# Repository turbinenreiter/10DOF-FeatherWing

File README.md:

# 10DOF-FeatherWing

This is a daughter-board for Adafruits Feather boards.  

It features:
  * 3-axis accelerometer
  * 3-axis gyroscope
  * 3-axis magnetometer
  * temperature sensor
  * pressure sensor
  * humidity sensor
  * 8 servo headers (PWR from BAT)
  * SPI header
  * UART header
  * one green and one red LED
  * one switch
  * GPIO#9 (A7) is connected to BAT to measure it's voltage

The board has been produced and tested.
  * all sensors work
  * red LED works
  * green LED is on when connected to USB, but not battery - no idea why

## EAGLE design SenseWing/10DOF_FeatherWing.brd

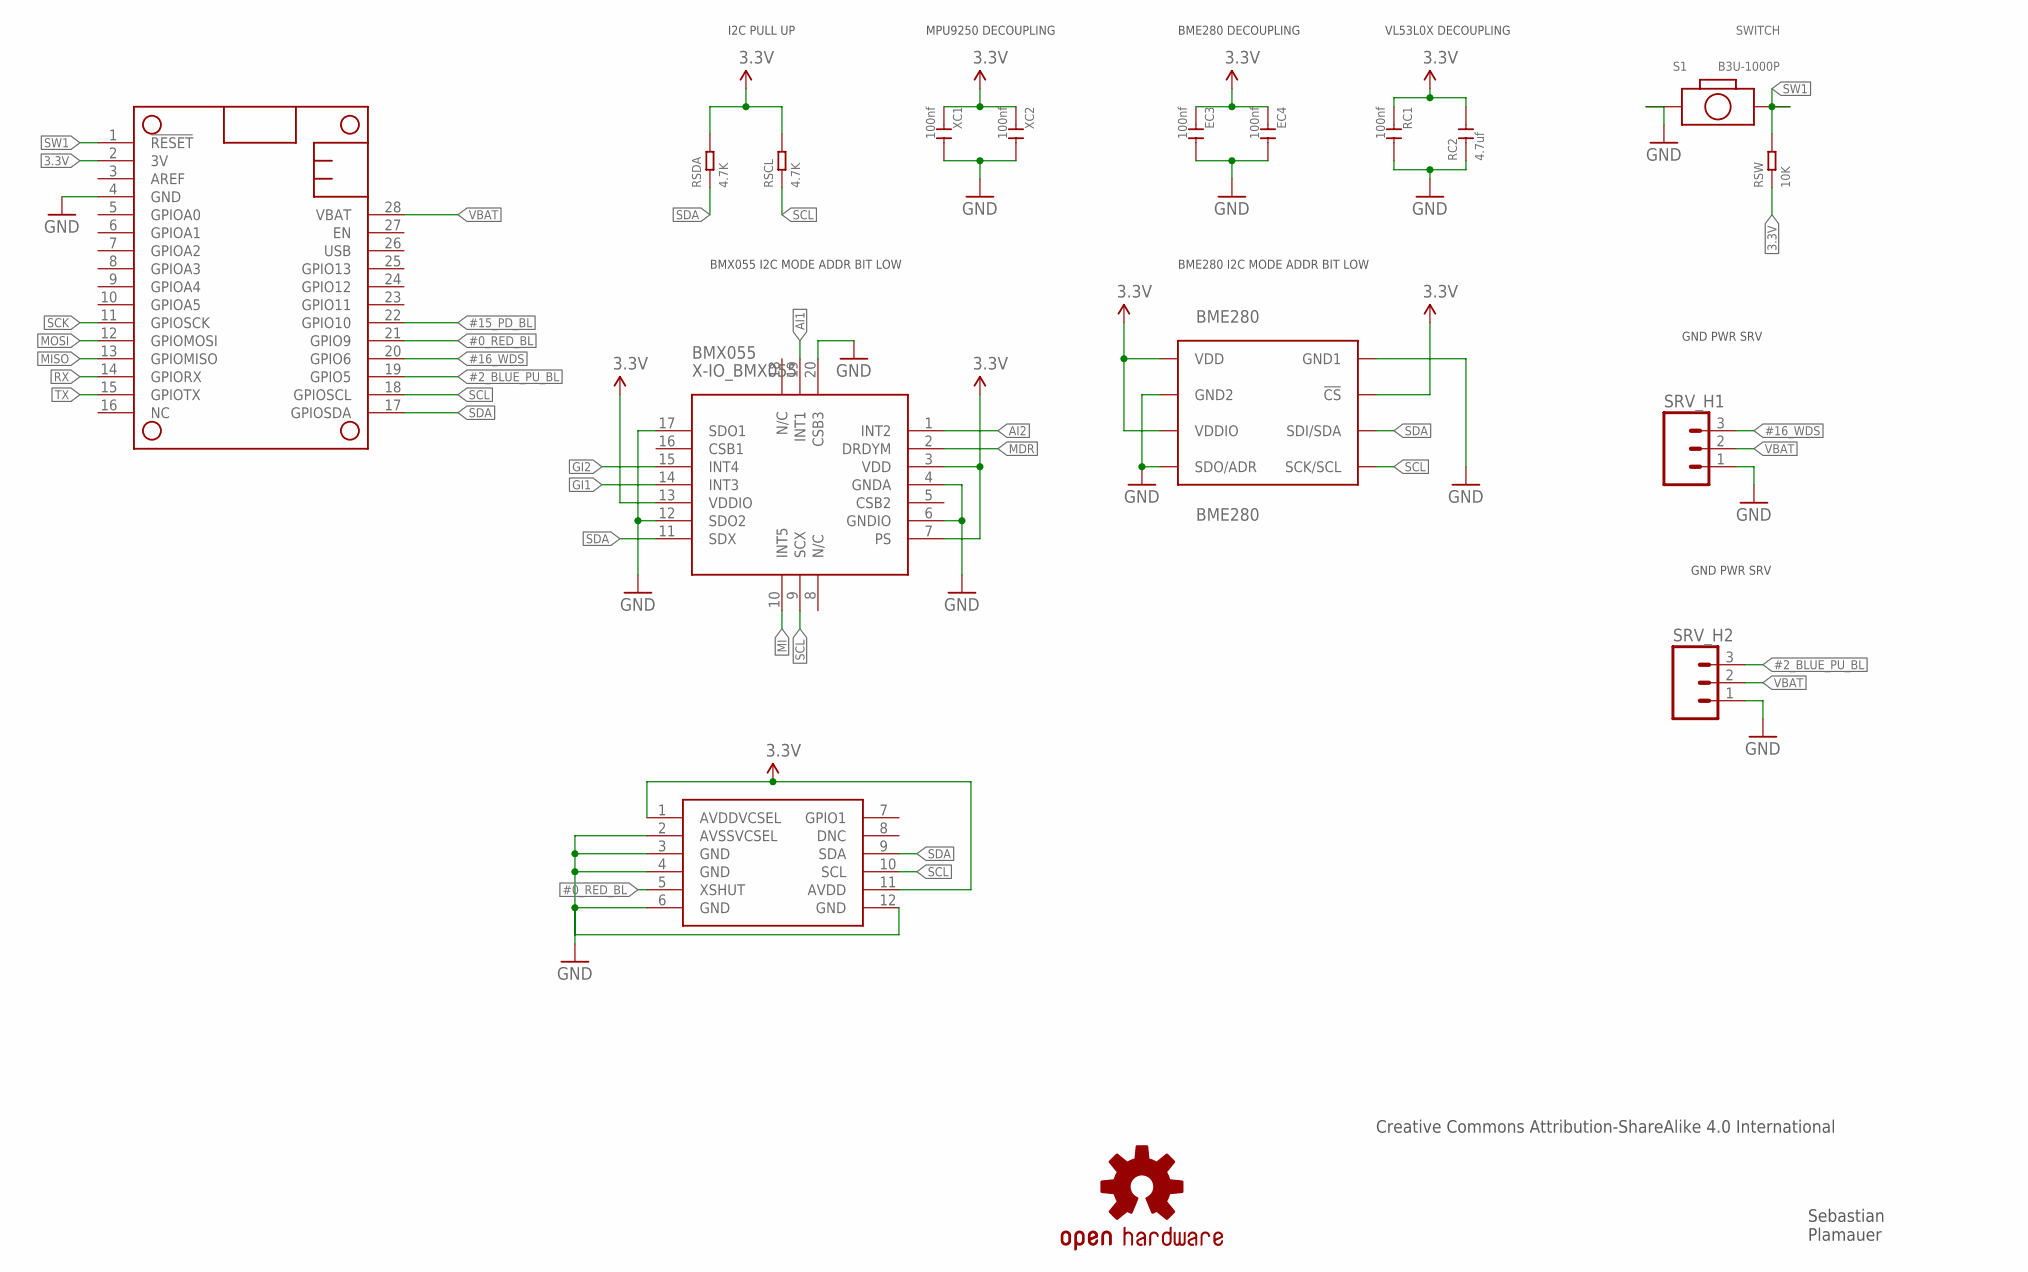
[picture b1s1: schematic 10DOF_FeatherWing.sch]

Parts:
BME280: BME280; BME280COMPONENTLIBRARY_BME280_LGA
BMX055: X-IO_BMX055
EC3, EC4: 100nf; C0603
LOGO1: OSHW-LOGOS; OSHW-LOGO-S
MS1: FEATHERWING
RC1: 100nf; C0603
RC2: 4.7uf; C0603
RSCL: 4.7K; R0603
RSDA: 4.7K; R0603
RSW: 10K; R0603
S1: B3U-1000P; SW2-SMD-3.0X2.5X1.2+0.4MM
SRV_H1, SRV_H2: M03PTH; 1X03
U$1: VL53L0X
XC1, XC2: 100nf; C0603

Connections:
3.3V: BME280.P$2 (!CS), BME280.P$6 (VDDIO), BME280.P$8 (VDD), BMX055.3 (VDD), BMX055.7 (PS), BMX055.13 (VDDIO), EC3.1, EC4.1, MS1.2 (3V), RC1.1, RC2.2, RSCL.2, RSDA.2, RSW.1, U$1.1 (AVDDVCSEL), U$1.11 (AVDD), XC1.1, XC2.1
#0_RED_BL: MS1.21 (GPIO9), U$1.5 (XSHUT)
#2_BLUE_PU_BL: MS1.19 (GPIO5), SRV_H2.3
#15_PD_BL: MS1.22 (GPIO10)
#16_WDS: MS1.20 (GPIO6), SRV_H1.3
AI1: BMX055.19 (INT1)
AI2: BMX055.1 (INT2)
GI1: BMX055.14 (INT3)
GI2: BMX055.15 (INT4)
GND: BME280.P$1 (GND1), BME280.P$5 (SDO/ADR), BME280.P$7 (GND2), BMX055.4 (GNDA), BMX055.6 (GNDIO), BMX055.12 (SDO2), BMX055.17 (SDO1), BMX055.20 (CSB3), EC3.2, EC4.2, MS1.4 (GND), RC1.2, RC2.1, S1.1, SRV_H1.1, SRV_H2.1, U$1.2 (AVSSVCSEL), U$1.3 (GND), U$1.4 (GND), U$1.6 (GND), U$1.12 (GND), XC1.2, XC2.2
MDR: BMX055.2 (DRDYM)
MI: BMX055.10 (INT5)
MISO: MS1.13 (GPIOMISO)
MOSI: MS1.12 (GPIOMOSI)
RX: MS1.14 (GPIORX)
SCK: MS1.11 (GPIOSCK)
SCL: BME280.P$4 (SCK/SCL), BMX055.9 (SCX), MS1.18 (GPIOSCL), RSCL.1, U$1.10 (SCL)
SDA: BME280.P$3 (SDI/SDA), BMX055.11 (SDX), MS1.17 (GPIOSDA), RSDA.1, U$1.9 (SDA)
SW1: MS1.1 (!RESET), RSW.2, S1.2
TX: MS1.15 (GPIOTX)
VBAT: MS1.28 (VBAT), SRV_H1.2, SRV_H2.2

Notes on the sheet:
I2C PULL UP
MPU9250 DECOUPLING
BME280 DECOUPLING
BME280 I2C MODE ADDR BIT LOW
GND PWR SRV
SWITCH
Sebastian Plamauer
Creative Commons Attribution-ShareAlike 4.0 International
VL53L0X DECOUPLING
BMX055 I2C MODE ADDR BIT LOW

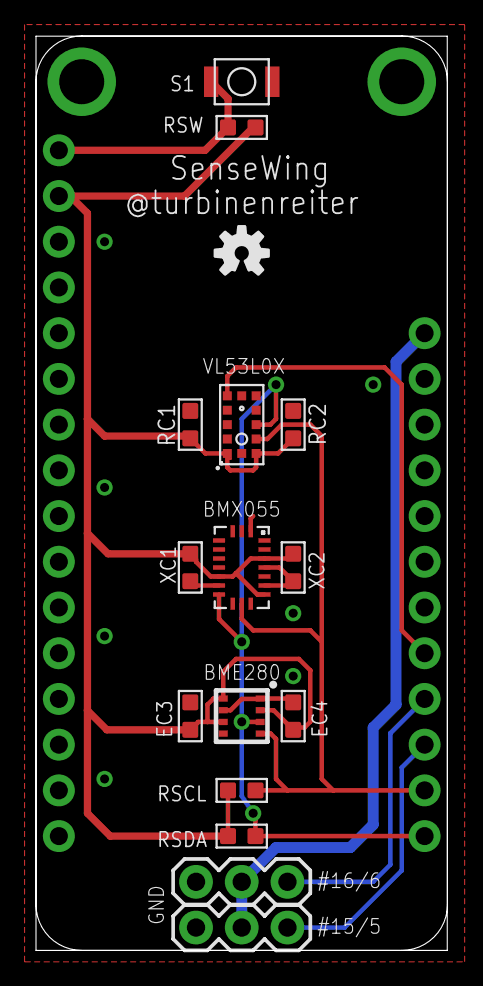
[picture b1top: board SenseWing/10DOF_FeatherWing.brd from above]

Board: 2 copper layers, 22.9 x 50.8 mm, 17 parts (0 on the bottom side), 9 nets.

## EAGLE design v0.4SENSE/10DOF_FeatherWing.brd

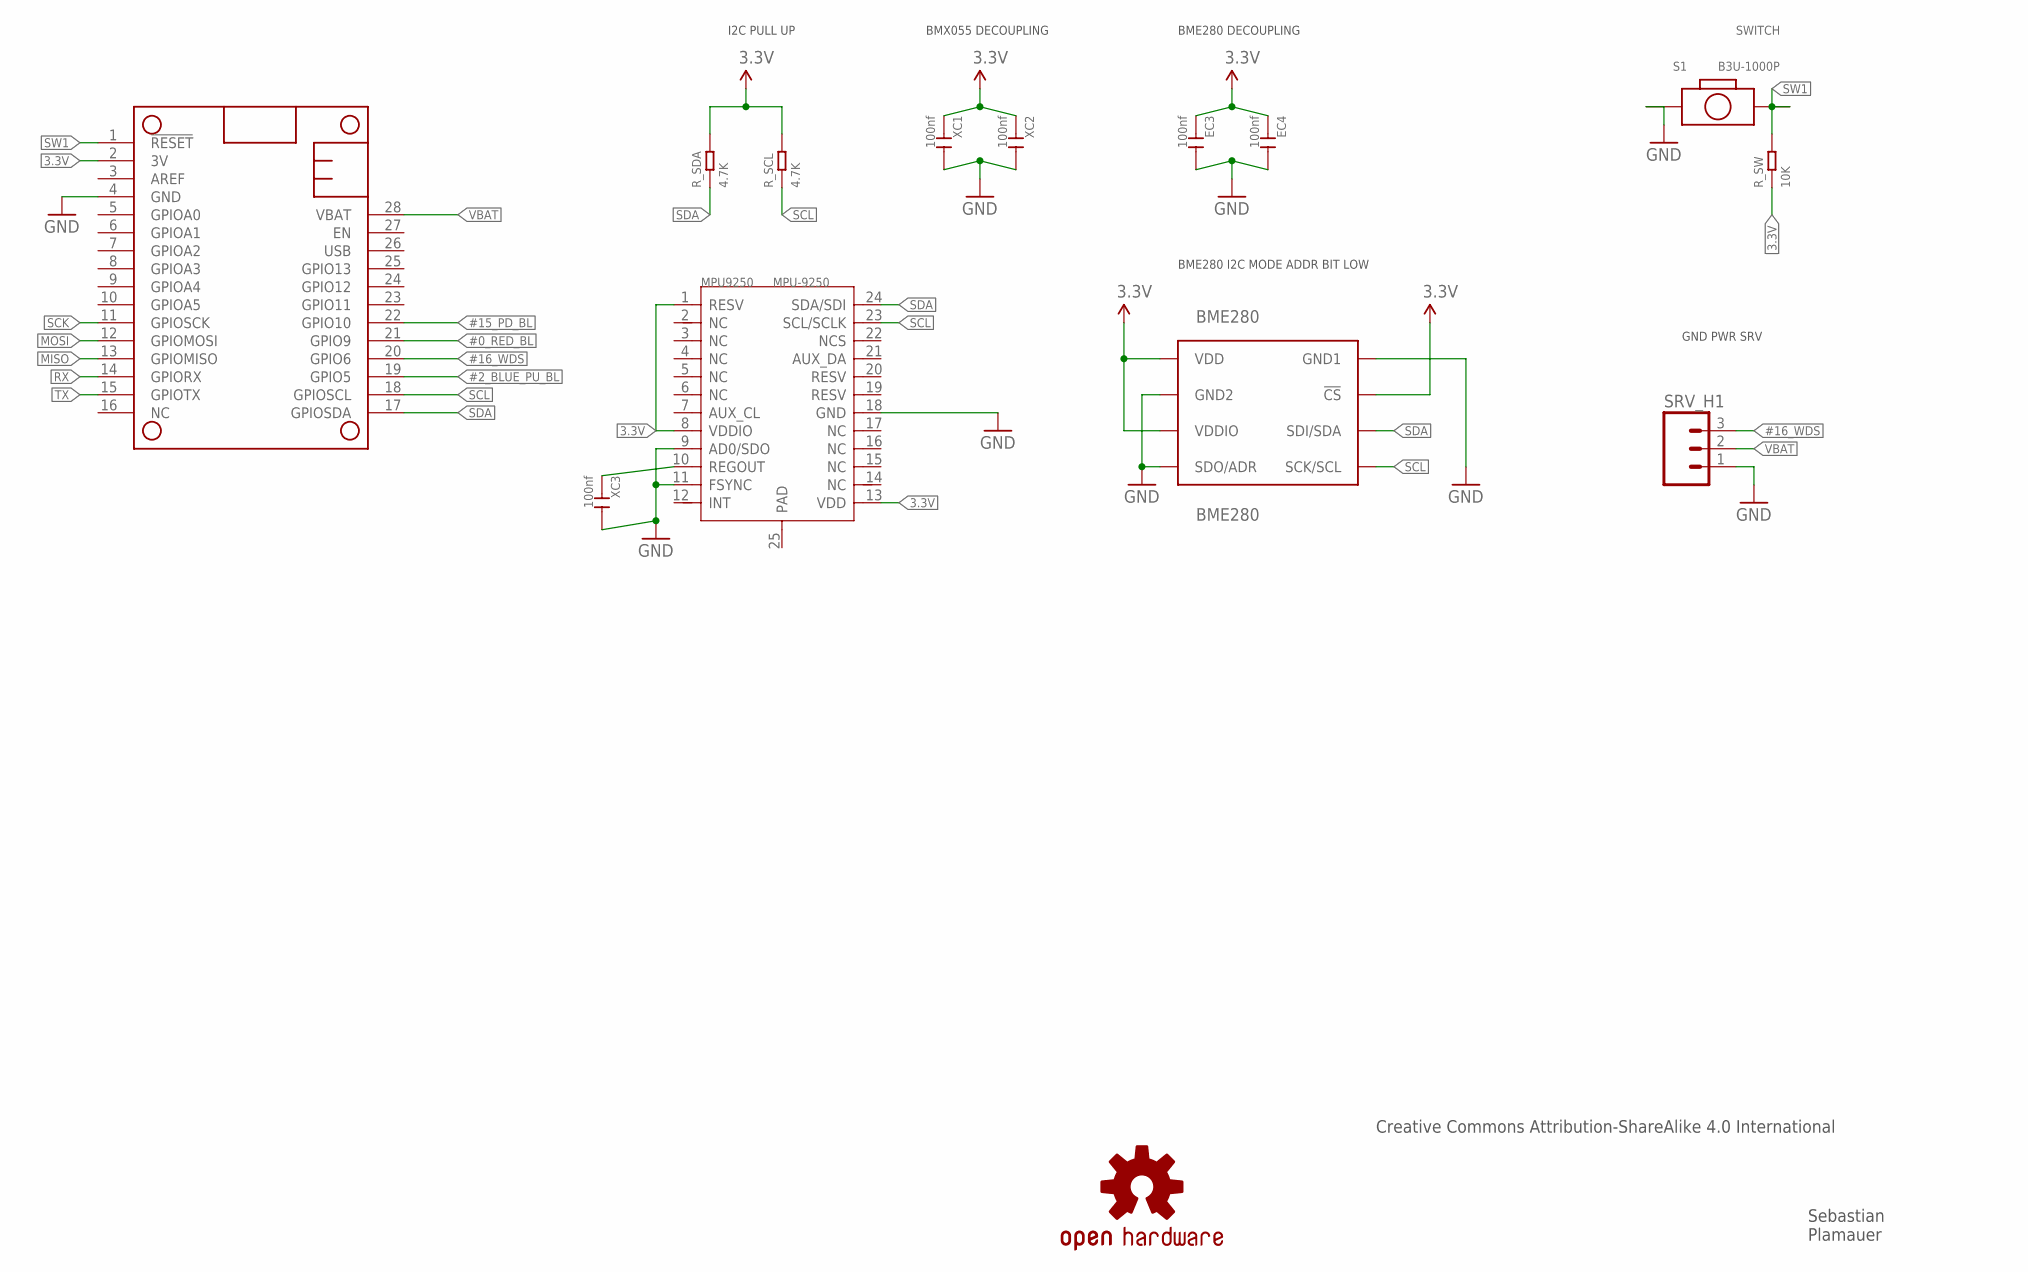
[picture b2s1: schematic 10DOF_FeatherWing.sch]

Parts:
BME280: BME280; BME280COMPONENTLIBRARY_BME280_LGA
EC3, EC4: 100nf; C0603
LOGO1: OSHW-LOGOS; OSHW-LOGO-S
MPU9250: MPU-9250; QFN24G-0.4-3X3MM
MS1: FEATHERWING
R_SCL: 4.7K; R0603
R_SDA: 4.7K; R0603
R_SW: 10K; R0603
S1: B3U-1000P; SW2-SMD-3.0X2.5X1.2+0.4MM
SRV_H1: M03PTH; 1X03
XC1, XC2, XC3: 100nf; C0603

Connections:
3.3V: BME280.P$2 (!CS), BME280.P$6 (VDDIO), BME280.P$8 (VDD), EC3.1, EC4.1, MPU9250.1 (RESV), MPU9250.8 (VDDIO), MPU9250.13 (VDD), MS1.2 (3V), R_SCL.2, R_SDA.2, R_SW.1, XC1.1, XC2.1
#0_RED_BL: MS1.21 (GPIO9)
#2_BLUE_PU_BL: MS1.19 (GPIO5)
#15_PD_BL: MS1.22 (GPIO10)
#16_WDS: MS1.20 (GPIO6), SRV_H1.3
GND: BME280.P$1 (GND1), BME280.P$5 (SDO/ADR), BME280.P$7 (GND2), EC3.2, EC4.2, MPU9250.9 (AD0/SDO), MPU9250.11 (FSYNC), MPU9250.18 (GND), MS1.4 (GND), S1.1, SRV_H1.1, XC1.2, XC2.2, XC3.2
MISO: MS1.13 (GPIOMISO)
MOSI: MS1.12 (GPIOMOSI)
unnamed: MPU9250.10 (REGOUT), XC3.1
RX: MS1.14 (GPIORX)
SCK: MS1.11 (GPIOSCK)
SCL: BME280.P$4 (SCK/SCL), MPU9250.23 (SCL/SCLK), MS1.18 (GPIOSCL), R_SCL.1
SDA: BME280.P$3 (SDI/SDA), MPU9250.24 (SDA/SDI), MS1.17 (GPIOSDA), R_SDA.1
SW1: MS1.1 (!RESET), R_SW.2, S1.2
TX: MS1.15 (GPIOTX)
VBAT: MS1.28 (VBAT), SRV_H1.2

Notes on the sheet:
I2C PULL UP
BMX055 DECOUPLING
BME280 DECOUPLING
BME280 I2C MODE ADDR BIT LOW
GND PWR SRV
SWITCH
Sebastian Plamauer
Creative Commons Attribution-ShareAlike 4.0 International

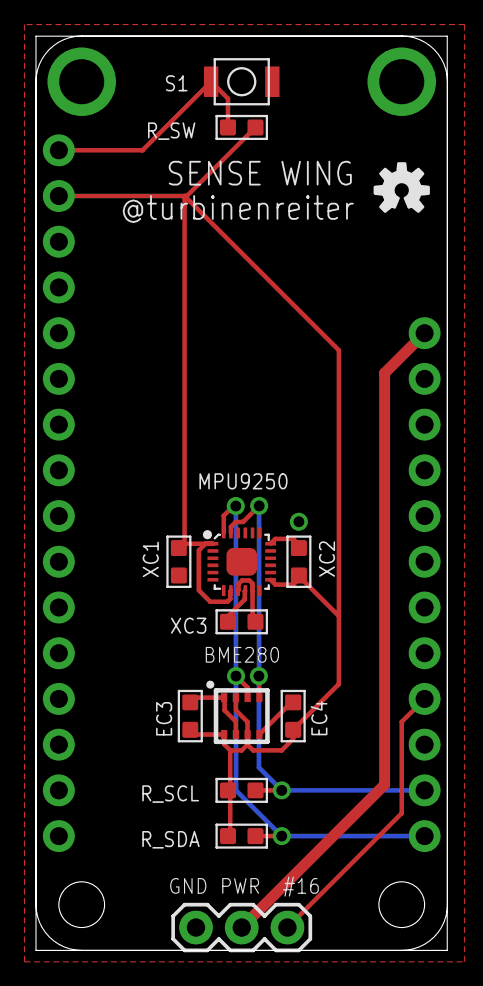
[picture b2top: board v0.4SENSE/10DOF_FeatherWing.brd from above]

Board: 2 copper layers, 22.9 x 50.8 mm, 14 parts (0 on the bottom side), 8 nets.

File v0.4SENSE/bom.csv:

"BME280","BME280","BME280COMPONENTLIBRARY_BME280","BME280COMPONENTLIBRARY_BME280_LGA"," ","1"
"EC3, EC4, XC1, XC2, XC3","100nf","CERAMIC-100NF-50V-10%-X7R(0603)","C0603","302010138","5"
"MPU9250","MPU-9250","MOTION/POSITION-MPU-9250(QFN24)","QFN24G-0.4-3X3MM","314990005","1"
"R_SCL, R_SDA","4.7K","SMD-RES-4.7K-5%-1/10W(0603)","R0603","301010290","2"
"R_SW","10K","SMD-RES-10K-1%-1/10W(0603)","R0603","301010299","1"
"S1","B3U-1000P","SMD-BUTTON-WITHOUT-BOSS-(2P-3X2.5MM)","SW2-SMD-3.0X2.5X1.2+0.4MM","311020047","1"

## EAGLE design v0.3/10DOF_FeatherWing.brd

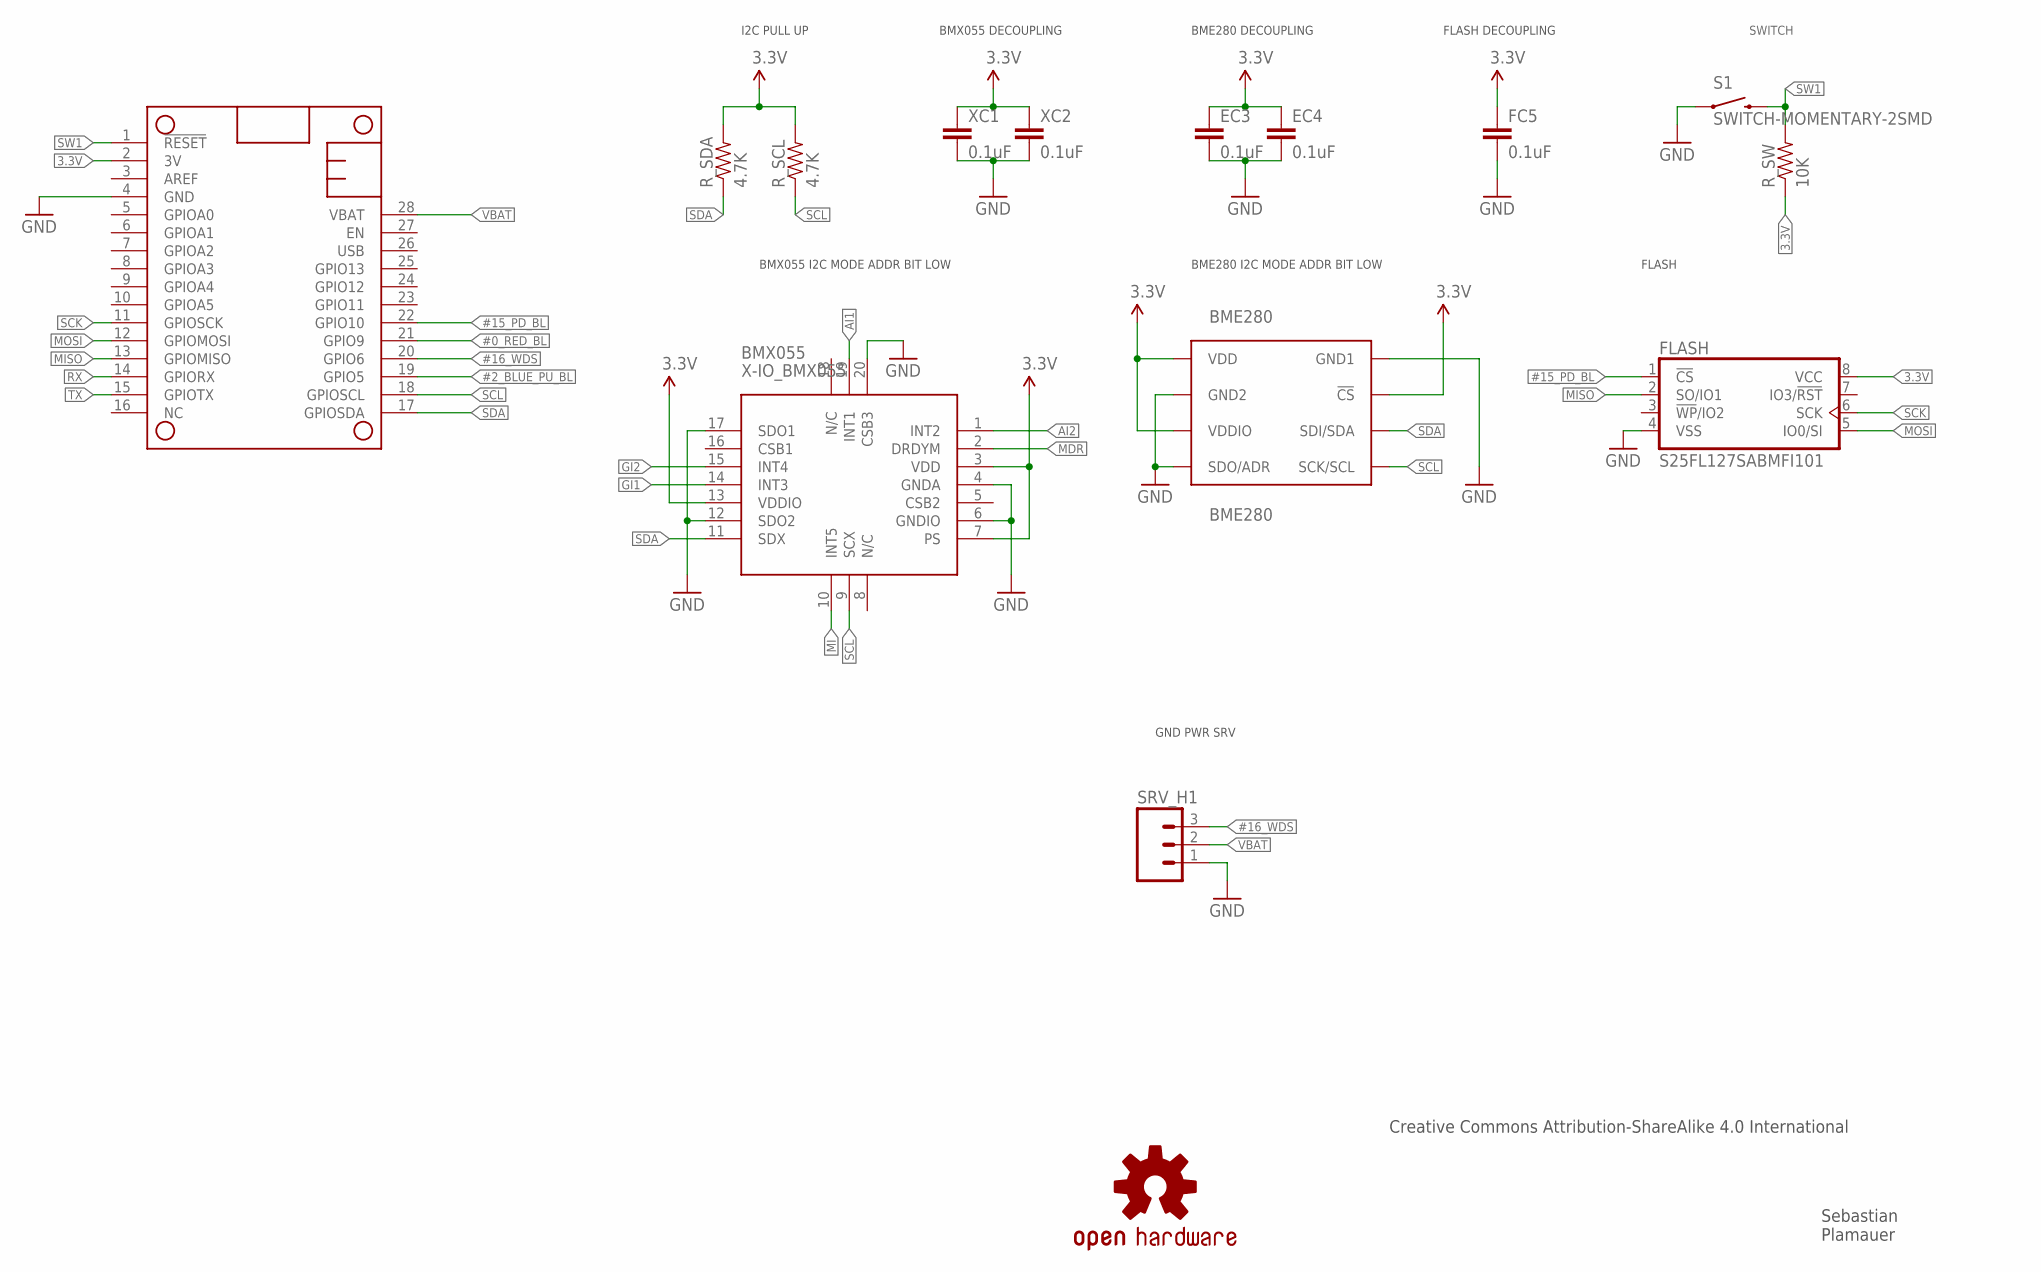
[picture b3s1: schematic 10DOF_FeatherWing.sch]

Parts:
BME280: BME280; BME280COMPONENTLIBRARY_BME280_LGA
BMX055: X-IO_BMX055
EC3, EC4: 0.1uF; 0603-CAP
FC5: 0.1uF; 0603-CAP
FLASH: S25FL127SABMFI101; SO08-S2A
LOGO1: OSHW-LOGOS; OSHW-LOGO-S
MS1: FEATHERWING
R_SCL: 4.7K; 0603-RES
R_SDA: 4.7K; 0603-RES
R_SW: 10K; 0603-RES
S1: SWITCH-MOMENTARY-2SMD; TACTILE-SWITCH-SMD
SRV_H1: M03PTH; 1X03
XC1, XC2: 0.1uF; 0603-CAP

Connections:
3.3V: BME280.P$2 (!CS), BME280.P$6 (VDDIO), BME280.P$8 (VDD), BMX055.3 (VDD), BMX055.7 (PS), BMX055.13 (VDDIO), EC3.1, EC4.1, FC5.1, FLASH.8 (VCC), MS1.2 (3V), R_SCL.2, R_SDA.2, R_SW.1, XC1.1, XC2.1
#0_RED_BL: MS1.21 (GPIO9)
#2_BLUE_PU_BL: MS1.19 (GPIO5)
#15_PD_BL: FLASH.1 (!CS!), MS1.22 (GPIO10)
#16_WDS: MS1.20 (GPIO6), SRV_H1.3
AI1: BMX055.19 (INT1)
AI2: BMX055.1 (INT2)
GI1: BMX055.14 (INT3)
GI2: BMX055.15 (INT4)
GND: BME280.P$1 (GND1), BME280.P$5 (SDO/ADR), BME280.P$7 (GND2), BMX055.4 (GNDA), BMX055.6 (GNDIO), BMX055.12 (SDO2), BMX055.17 (SDO1), BMX055.20 (CSB3), EC3.2, EC4.2, FC5.2, FLASH.4 (VSS), MS1.4 (GND), S1.1, SRV_H1.1, XC1.2, XC2.2
MDR: BMX055.2 (DRDYM)
MI: BMX055.10 (INT5)
MISO: FLASH.2 (SO/IO1), MS1.13 (GPIOMISO)
MOSI: FLASH.5 (IO0/SI), MS1.12 (GPIOMOSI)
RX: MS1.14 (GPIORX)
SCK: FLASH.6 (SCK), MS1.11 (GPIOSCK)
SCL: BME280.P$4 (SCK/SCL), BMX055.9 (SCX), MS1.18 (GPIOSCL), R_SCL.1
SDA: BME280.P$3 (SDI/SDA), BMX055.11 (SDX), MS1.17 (GPIOSDA), R_SDA.1
SW1: MS1.1 (!RESET), R_SW.2, S1.3 (2)
TX: MS1.15 (GPIOTX)
VBAT: MS1.28 (VBAT), SRV_H1.2

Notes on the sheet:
I2C PULL UP
BMX055 DECOUPLING
BME280 DECOUPLING
BME280 I2C MODE ADDR BIT LOW
BMX055 I2C MODE ADDR BIT LOW
GND PWR SRV
SWITCH
Sebastian Plamauer
Creative Commons Attribution-ShareAlike 4.0 International
FLASH
FLASH DECOUPLING

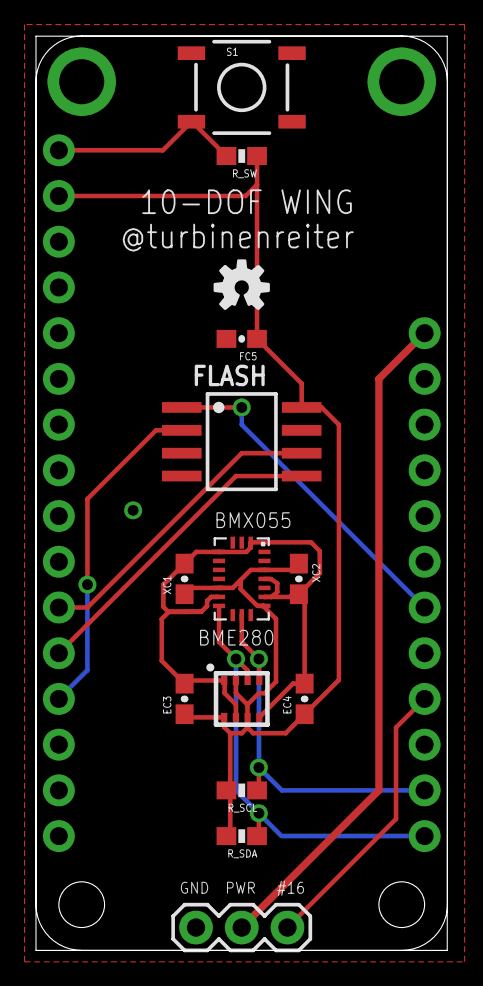
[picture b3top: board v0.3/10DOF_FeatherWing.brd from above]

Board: 2 copper layers, 22.9 x 50.8 mm, 15 parts (0 on the bottom side), 11 nets.

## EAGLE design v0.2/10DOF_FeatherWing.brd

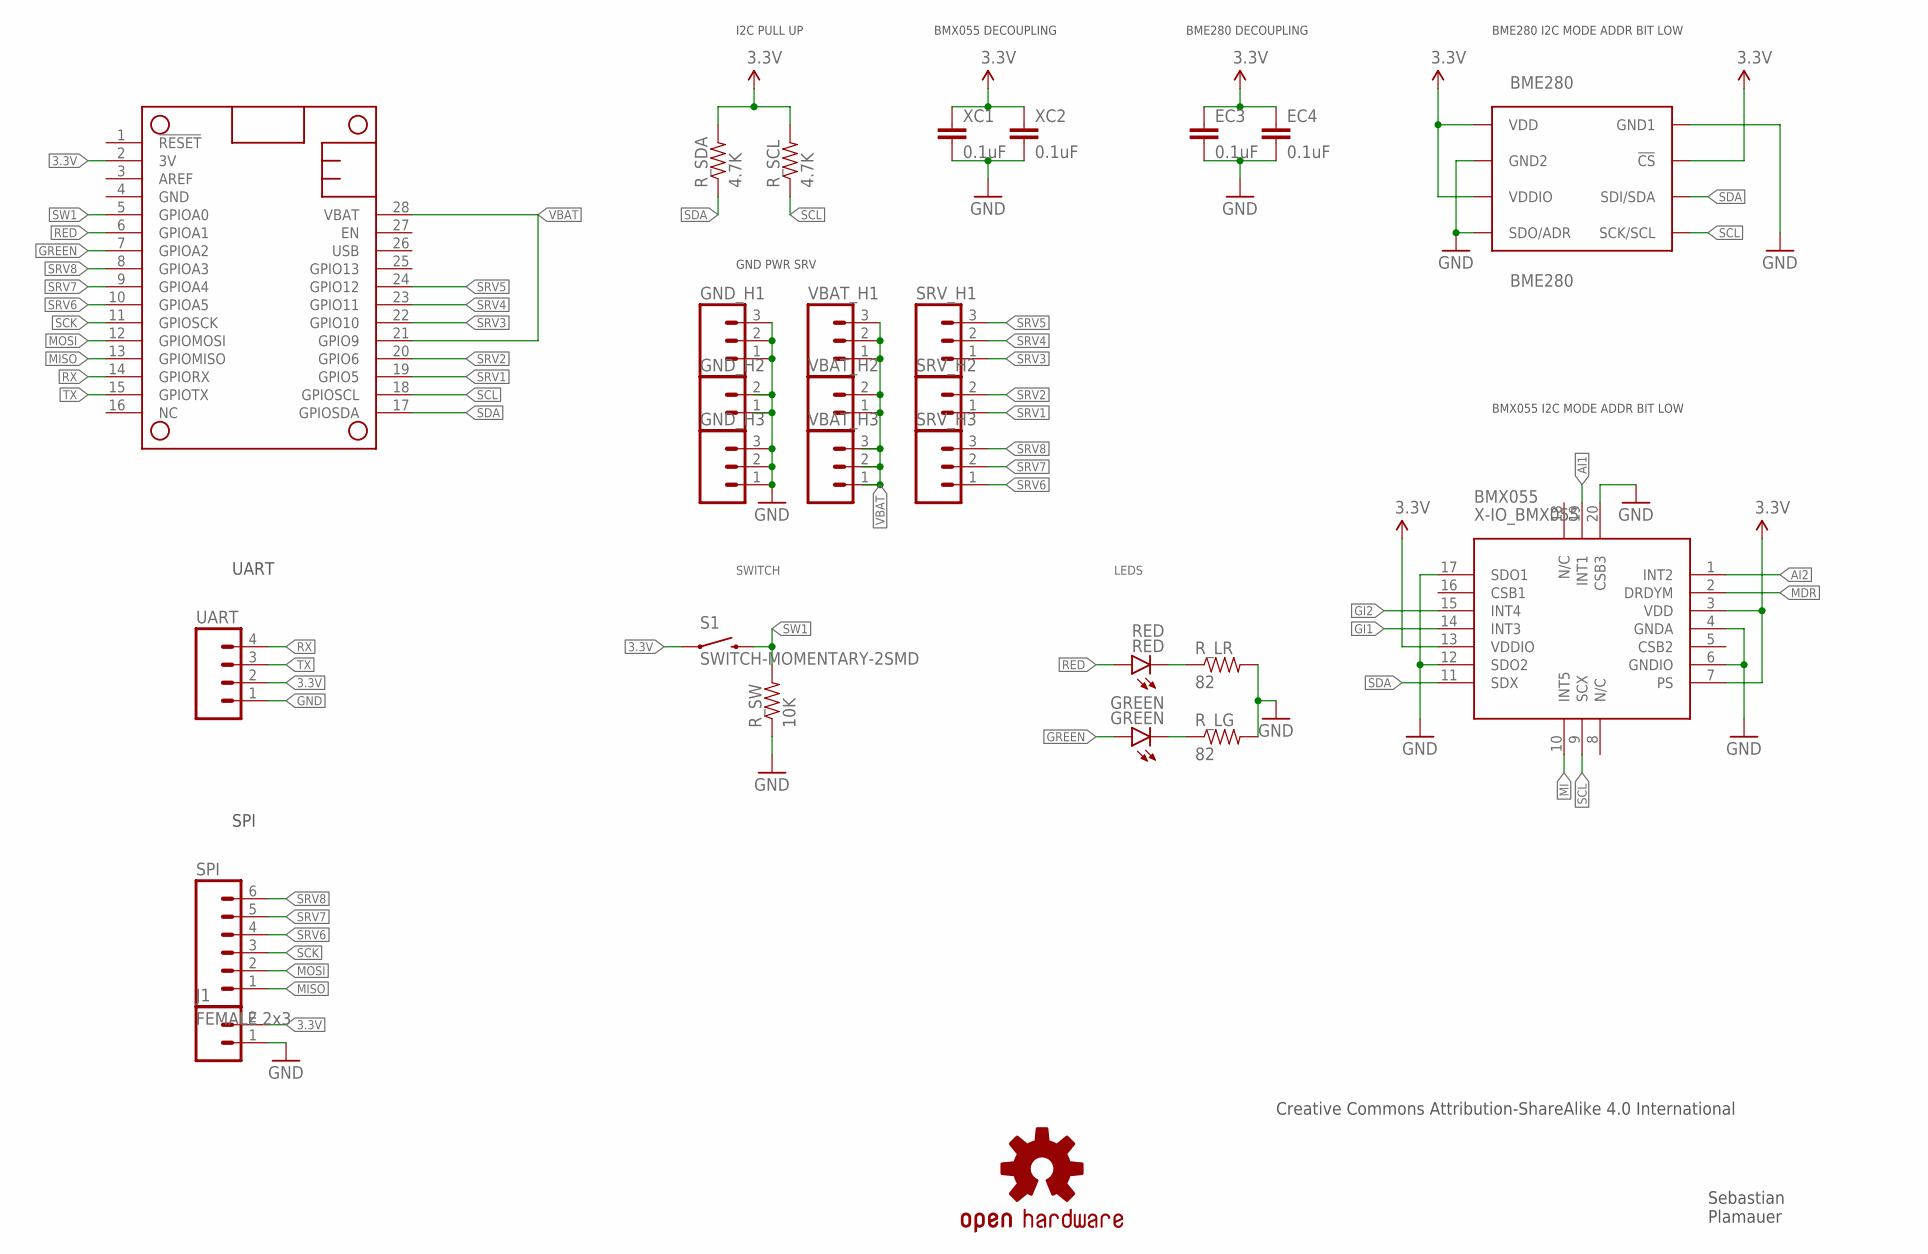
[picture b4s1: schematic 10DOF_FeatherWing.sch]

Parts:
BME280: BME280; BME280COMPONENTLIBRARY_BME280_LGA
BMX055: X-IO_BMX055
EC3, EC4: 0.1uF; 0603-CAP
GND_H1, GND_H3: M03PTH; 1X03
GND_H2: M02PTH; 1X02
GREEN: GREEN; LED-0603
J1: M02PTH; 1X02
LOGO1: OSHW-LOGOS; OSHW-LOGO-S
MS1: FEATHERWING
RED: RED; LED-0603
R_LG: 82; 0603-RES
R_LR: 82; 0603-RES
R_SCL: 4.7K; 0603-RES
R_SDA: 4.7K; 0603-RES
R_SW: 10K; 0603-RES
S1: SWITCH-MOMENTARY-2SMD; TACTILE-SWITCH-SMD
SPI: FEMALE 2x3; 1X06
SRV_H1, SRV_H3: M03PTH; 1X03
SRV_H2: M02PTH; 1X02
UART: M04PTH; 1X04
VBAT_H1, VBAT_H3: M03PTH; 1X03
VBAT_H2: M02PTH; 1X02
XC1, XC2: 0.1uF; 0603-CAP

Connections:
3.3V: BME280.P$2 (!CS), BME280.P$6 (VDDIO), BME280.P$8 (VDD), BMX055.3 (VDD), BMX055.7 (PS), BMX055.13 (VDDIO), EC3.1, EC4.1, J1.2, MS1.2 (3V), R_SCL.2, R_SDA.2, S1.1, UART.2, XC1.1, XC2.1
AI1: BMX055.19 (INT1)
AI2: BMX055.1 (INT2)
GI1: BMX055.14 (INT3)
GI2: BMX055.15 (INT4)
GND: BME280.P$1 (GND1), BME280.P$5 (SDO/ADR), BME280.P$7 (GND2), BMX055.4 (GNDA), BMX055.6 (GNDIO), BMX055.12 (SDO2), BMX055.17 (SDO1), BMX055.20 (CSB3), EC3.2, EC4.2, GND_H1.1, GND_H1.2, GND_H1.3, GND_H2.1, GND_H2.2, GND_H3.1, GND_H3.2, GND_H3.3, J1.1, MS1.4 (GND), R_LG.2, R_LR.2, R_SW.1, UART.1, XC1.2, XC2.2
GREEN: GREEN.A, MS1.7 (GPIOA2)
MDR: BMX055.2 (DRDYM)
MI: BMX055.10 (INT5)
MISO: MS1.13 (GPIOMISO), SPI.1
MOSI: MS1.12 (GPIOMOSI), SPI.2
unnamed: GREEN.C, R_LG.1
unnamed: RED.C, R_LR.1
RED: MS1.6 (GPIOA1), RED.A
RX: MS1.14 (GPIORX), UART.4
SCK: MS1.11 (GPIOSCK), SPI.3
SCL: BME280.P$4 (SCK/SCL), BMX055.9 (SCX), MS1.18 (GPIOSCL), R_SCL.1
SDA: BME280.P$3 (SDI/SDA), BMX055.11 (SDX), MS1.17 (GPIOSDA), R_SDA.1
SRV1: MS1.19 (GPIO5), SRV_H2.1
SRV2: MS1.20 (GPIO6), SRV_H2.2
SRV3: MS1.22 (GPIO10), SRV_H1.1
SRV4: MS1.23 (GPIO11), SRV_H1.2
SRV5: MS1.24 (GPIO12), SRV_H1.3
SRV6: MS1.10 (GPIOA5), SPI.4, SRV_H3.1
SRV7: MS1.9 (GPIOA4), SPI.5, SRV_H3.2
SRV8: MS1.8 (GPIOA3), SPI.6, SRV_H3.3
SW1: MS1.5 (GPIOA0), R_SW.2, S1.3 (2)
TX: MS1.15 (GPIOTX), UART.3
VBAT: MS1.21 (GPIO9), MS1.28 (VBAT), VBAT_H1.1, VBAT_H1.2, VBAT_H1.3, VBAT_H2.1, VBAT_H2.2, VBAT_H3.1, VBAT_H3.2, VBAT_H3.3

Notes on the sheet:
I2C PULL UP
BMX055 DECOUPLING
BME280 DECOUPLING
BME280 I2C MODE ADDR BIT LOW
BMX055 I2C MODE ADDR BIT LOW
GND PWR SRV
SWITCH
LEDS
UART
Sebastian Plamauer
Creative Commons Attribution-ShareAlike 4.0 International
SPI

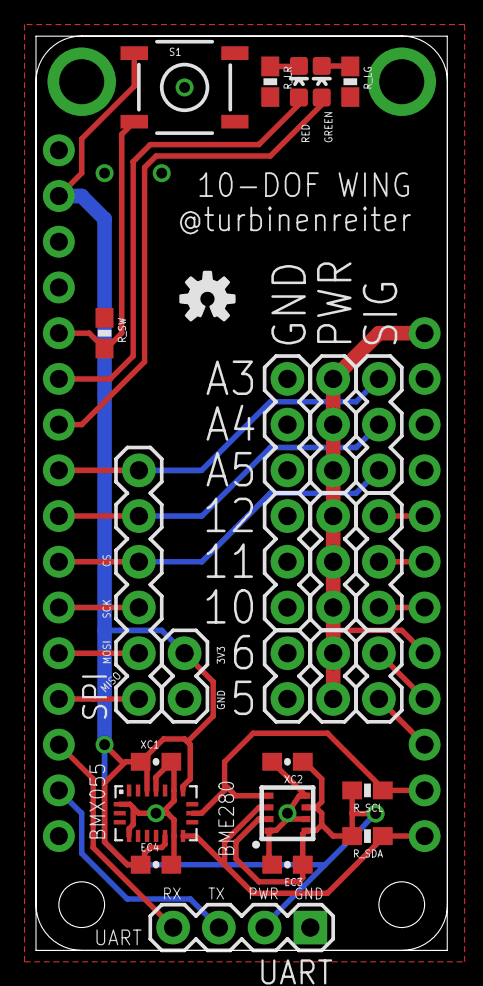
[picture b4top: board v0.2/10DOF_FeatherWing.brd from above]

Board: 2 copper layers, 22.9 x 50.8 mm, 28 parts (0 on the bottom side), 23 nets.

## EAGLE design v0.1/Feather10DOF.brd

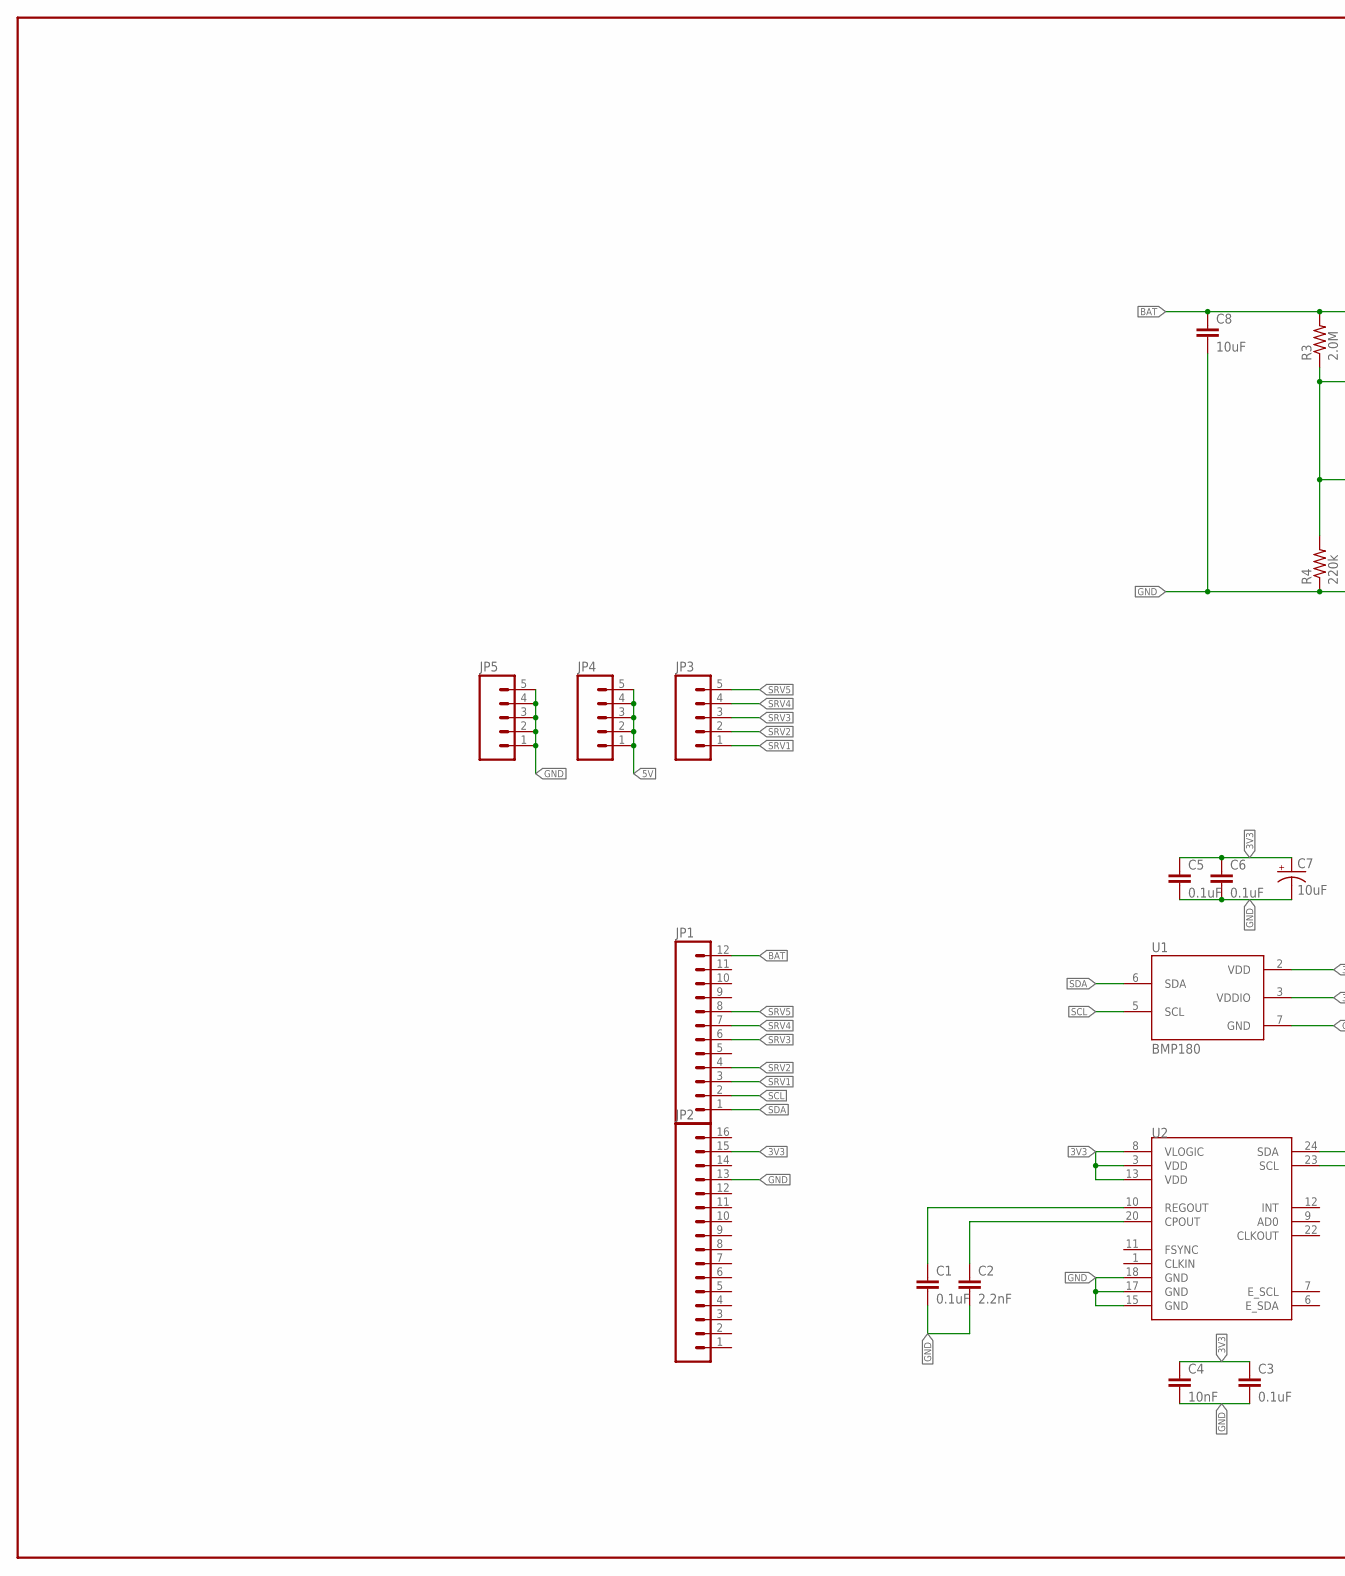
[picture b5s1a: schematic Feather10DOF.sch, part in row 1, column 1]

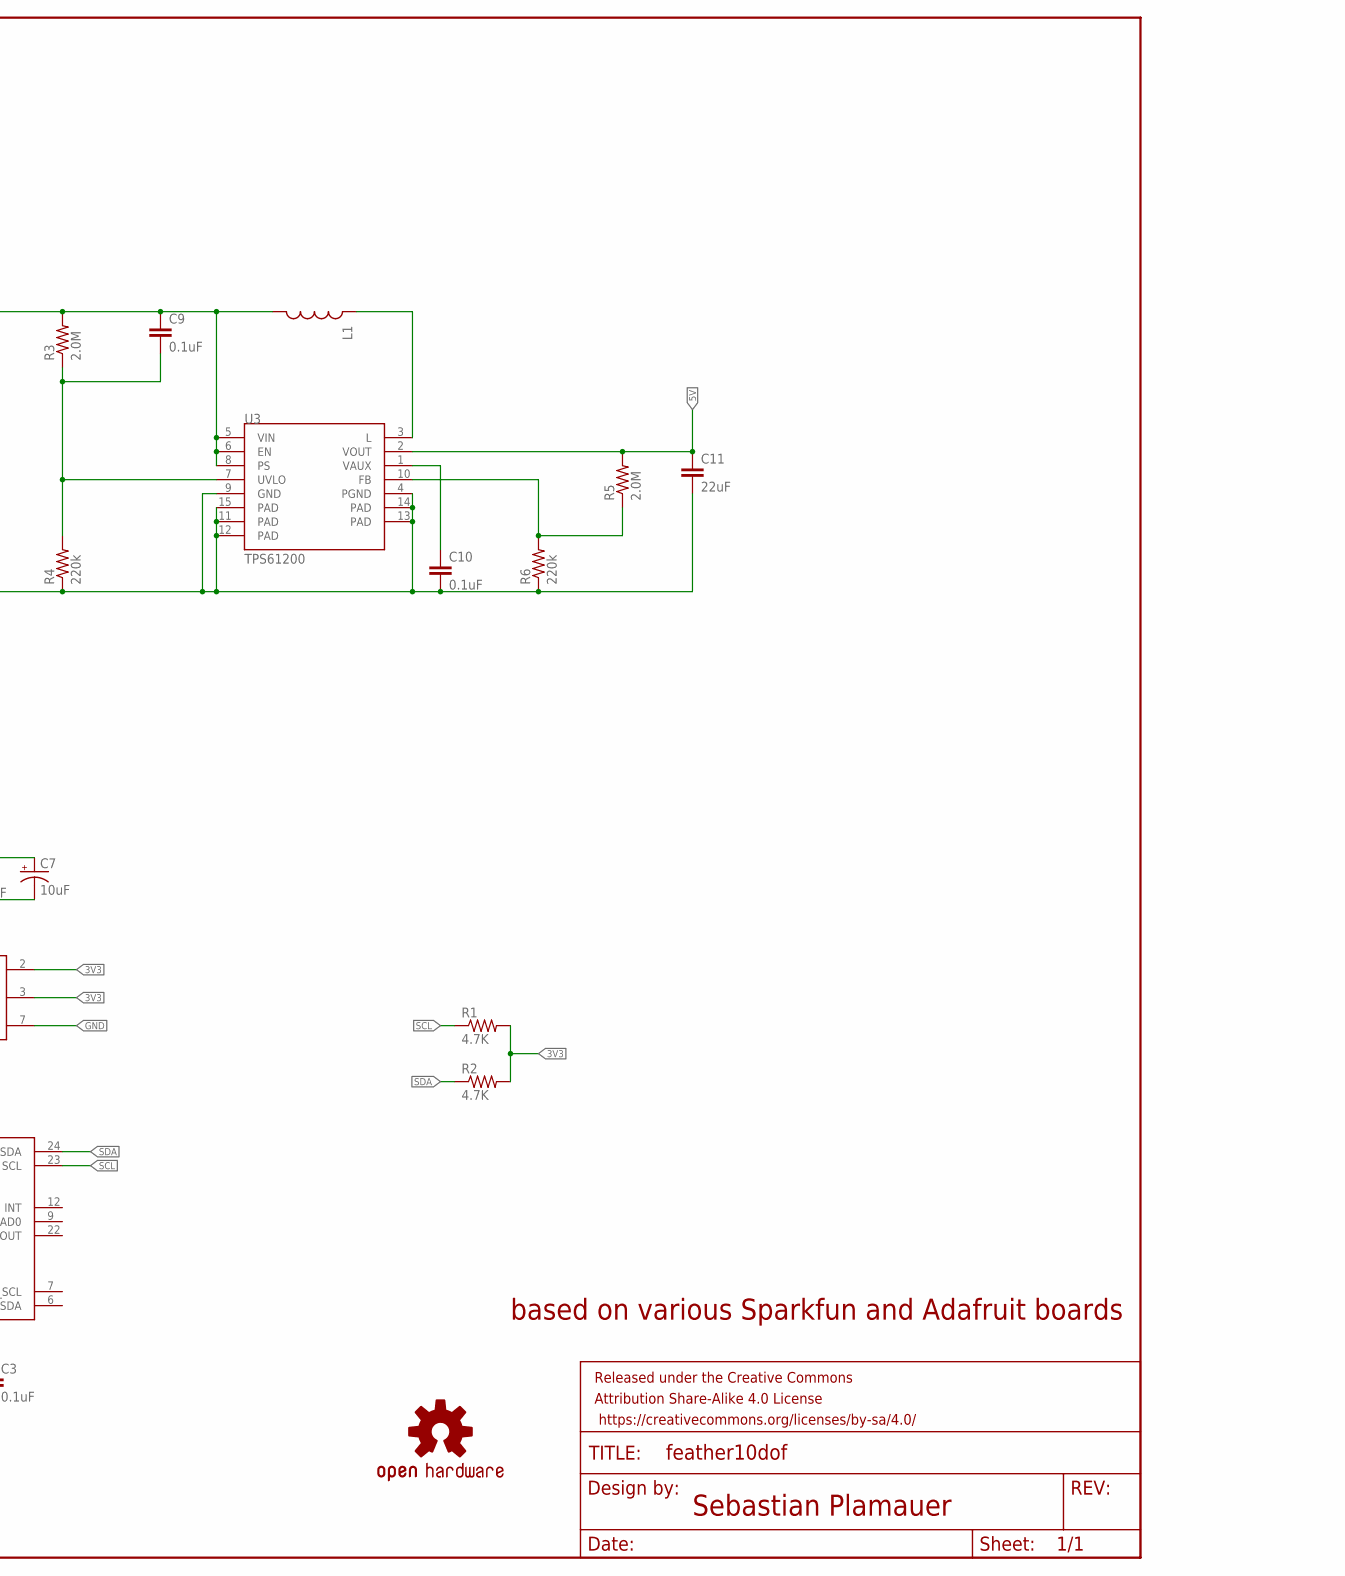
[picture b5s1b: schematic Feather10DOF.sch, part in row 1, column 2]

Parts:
C1, C3, C5, C6, C9, C10: 0.1uF; 0603-CAP
C2: 2.2nF; 0603-CAP
C4: 10nF; 0603-CAP
C7: 10uF; 0603-POL
C8: 10uF; 0603-CAP
C11: 22uF; 0805
FRAME1: FRAME-LEDGER; CREATIVE_COMMONS
JP1: M12PTH; 1X12
JP2: M16PTH; 1X16
JP3, JP4, JP5: M05PTH; 1X05
L1: INDUCTOR1007; 1007
LOGO1: OSHW-LOGOL; OSHW-LOGO-L
R1, R2: 4.7K; 0603-RES
R3, R5: 2.0M; 0603-RES
R4, R6: 220k; 0603-RES
U1: BMP180
U2: MPU-9150QFN-24-NP; QFN-24-NP
U3: TPS61200; QFN-10_PAD

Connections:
3V3: C3.1, C4.1, C5.1, C6.1, C7.A (+), JP2.15, R1.2, R2.2, U1.2 (VDD), U1.3 (VDDIO), U2.3 (VDD), U2.8 (VLOGIC), U2.13 (VDD)
5V: C11.1, JP4.1, JP4.2, JP4.3, JP4.4, JP4.5, R5.2, U3.2 (VOUT)
BAT: C8.1, C9.1, JP1.12, L1.2, R3.2, U3.5 (VIN), U3.6 (EN), U3.8 (PS)
GND: C1.2, C2.2, C3.2, C4.2, C5.2, C6.2, C7.K (-), C8.2, C10.2, C11.2, JP2.13, JP5.1, JP5.2, JP5.3, JP5.4, JP5.5, R4.1, R6.1, U1.7 (GND), U2.15 (GND), U2.17 (GND), U2.18 (GND), U3.4 (PGND), U3.9 (GND), U3.11 (PAD), U3.12 (PAD), U3.13 (PAD), U3.14 (PAD), U3.15 (PAD)
unnamed: C2.1, U2.20 (CPOUT)
unnamed: C1.1, U2.10 (REGOUT)
unnamed: R5.1, R6.2, U3.10 (FB)
unnamed: C9.2, R3.1, R4.2, U3.7 (UVLO)
unnamed: L1.1, U3.3 (L)
unnamed: C10.1, U3.1 (VAUX)
SCL: JP1.2, R1.1, U1.5 (SCL), U2.23 (SCL)
SDA: JP1.1, R2.1, U1.6 (SDA), U2.24 (SDA)
SRV1: JP1.3, JP3.1
SRV2: JP1.4, JP3.2
SRV3: JP1.6, JP3.3
SRV4: JP1.7, JP3.4
SRV5: JP1.8, JP3.5

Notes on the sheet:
Sebastian Plamauer
based on various Sparkfun and Adafruit boards

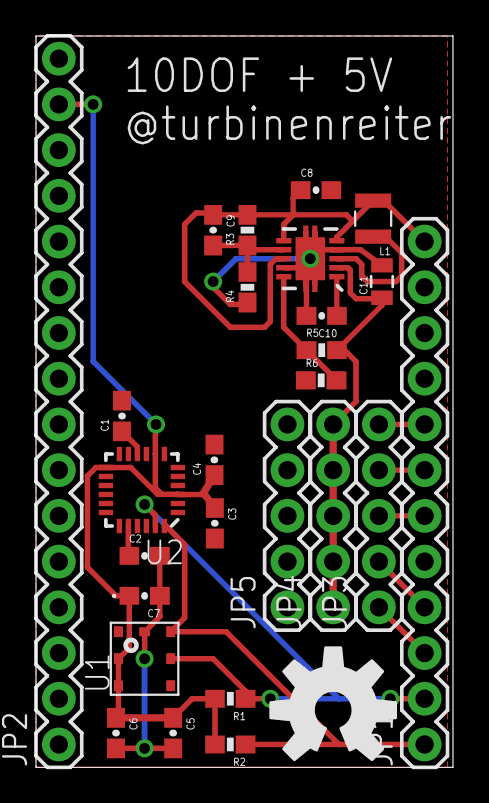
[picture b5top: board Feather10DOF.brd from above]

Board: 2 copper layers, 23.2 x 40.6 mm, 28 parts (0 on the bottom side), 17 nets.

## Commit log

2016-01-21 added license
2016-01-21 added v0.2
2016-01-21 removed files from root dir
2016-01-21 removed eagle.epf from root dir
2016-01-22 updatet v2 with more servo headers, better routing
2016-01-23 added SPI header
2016-02-11 added test program
2016-02-12 code cleanup and added liveplotting program
2016-07-11 add v4
2016-09-08 added v5 SenseWing

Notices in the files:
parts and their libraries:
SparkFun-Connectors: Licensing: Creative Commons ShareAlike 4.0 International - https://creativecommons.org/licenses/by-sa/4.0
SparkFun-Aesthetics: Released under the Creative Commons Attribution Share-Alike 4.0 License
SparkFun-Aesthetics: https://creativecommons.org/licenses/by-sa/4.0
